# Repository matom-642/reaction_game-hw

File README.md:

# reaction_game-hw
Simple two button reaction game based on raspberry pi pico.

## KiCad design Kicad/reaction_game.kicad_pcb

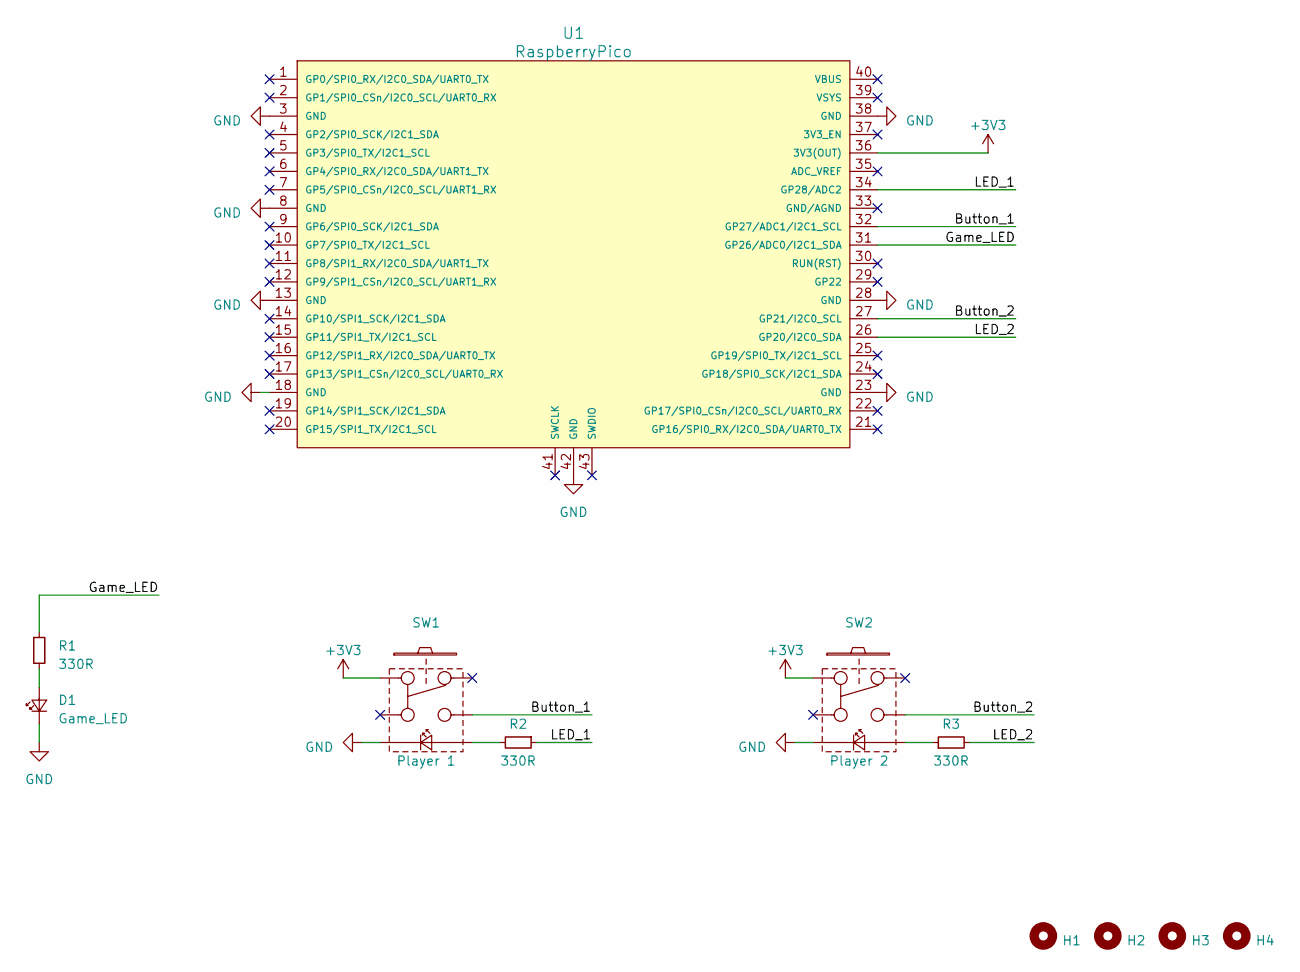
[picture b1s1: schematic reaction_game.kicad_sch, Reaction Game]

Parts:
D1: Game_LED; LED_D8.0mm
H1, H2, H3, H4: MountingHole_NPTH; MountingHole_3.2mm_M3_Pad_NPTH
R1, R2, R3: 330R; 0603C-KICAD
SW1: Player 1; SW_PUSH-SP86N-A1-5-01
SW2: Player 2; SW_PUSH-SP86N-A1-5-01
U1: RaspberryPico; Raspberry_Pi_Pico_Rev3-THT_Offset

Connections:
+3V3: SW1.1, SW2.1, U1.36 (3V3(OUT))
/Button_1: SW1.3, U1.32 (GP27/ADC1/I2C1_SCL)
/Button_2: SW2.3, U1.27 (GP21/I2C0_SCL)
/Game_LED: R1.1, U1.31 (GP26/ADC0/I2C1_SDA)
/LED_1: R2.1, U1.34 (GP28/ADC2)
/LED_2: R3.2, U1.26 (GP20/I2C0_SDA)
GND: D1.1 (K), SW1.4 (K), SW2.4 (K), U1.3 (GND), U1.8 (GND), U1.13 (GND), U1.18 (GND), U1.23 (GND), U1.28 (GND), U1.38 (GND), U1.42 (GND)
unnamed: D1.2 (A), R1.2
unnamed: R2.2, SW1.5 (A)
unnamed: R3.1, SW2.5 (A)

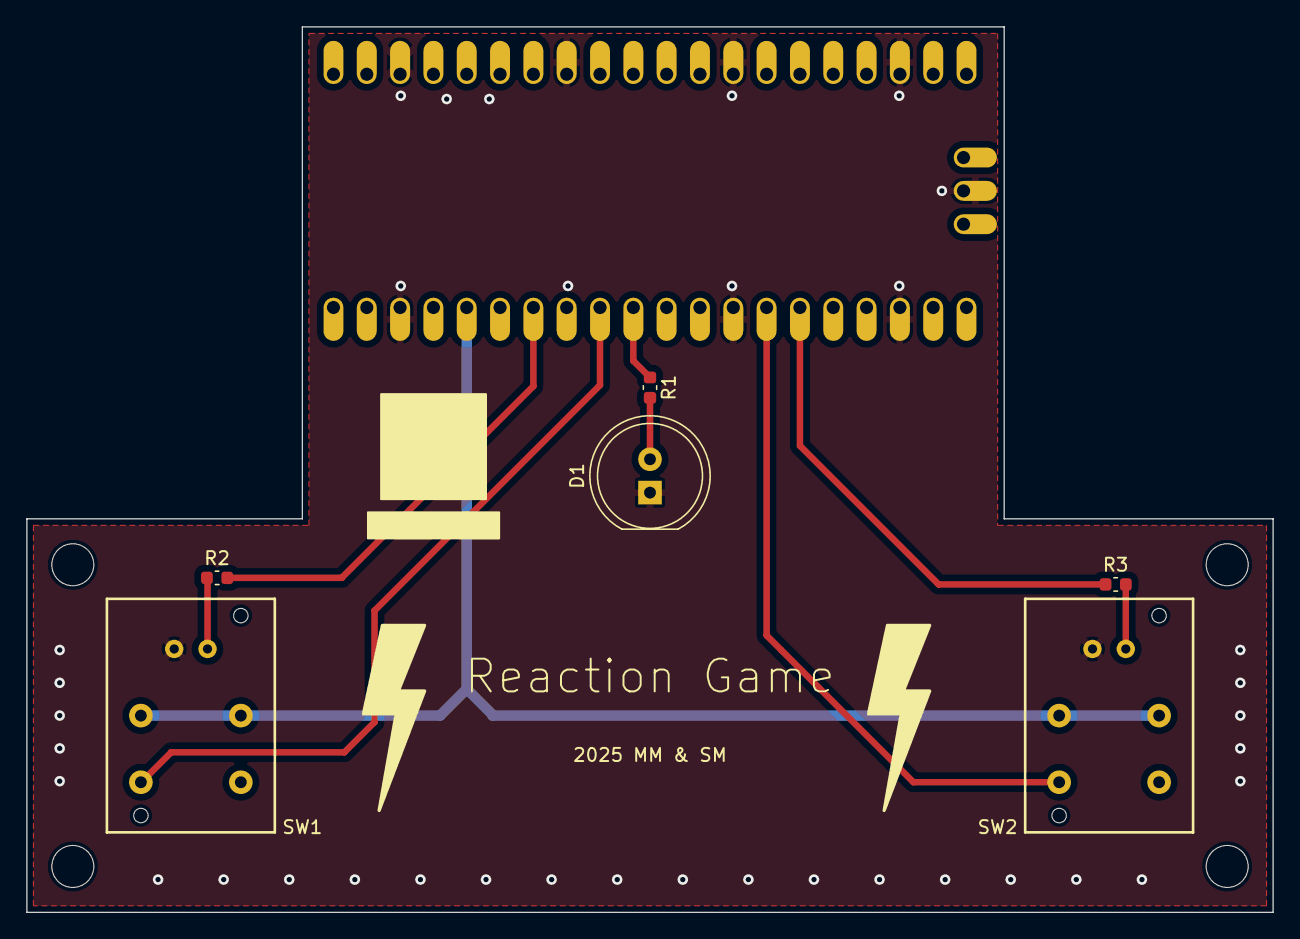
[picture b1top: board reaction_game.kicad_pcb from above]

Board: 2 copper layers, 95.0 x 67.5 mm, 11 parts (1 on the bottom side), 10 nets.

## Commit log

2025-01-05 Schematic design complete
2025-01-05 PCB & initial placement
    - assigned footprints
    - created PCB
    - initial placement of the components
2025-01-06 3D models, placement
2025-01-06 Finished routing
2025-01-06 Silkscreen
2025-01-06 Silkscreen
    - added second lightning bolt
2025-01-06 Project modification
    - rule setup
2025-01-13 Fixed Pico
    - flipped pico
2025-01-13 Pin change
